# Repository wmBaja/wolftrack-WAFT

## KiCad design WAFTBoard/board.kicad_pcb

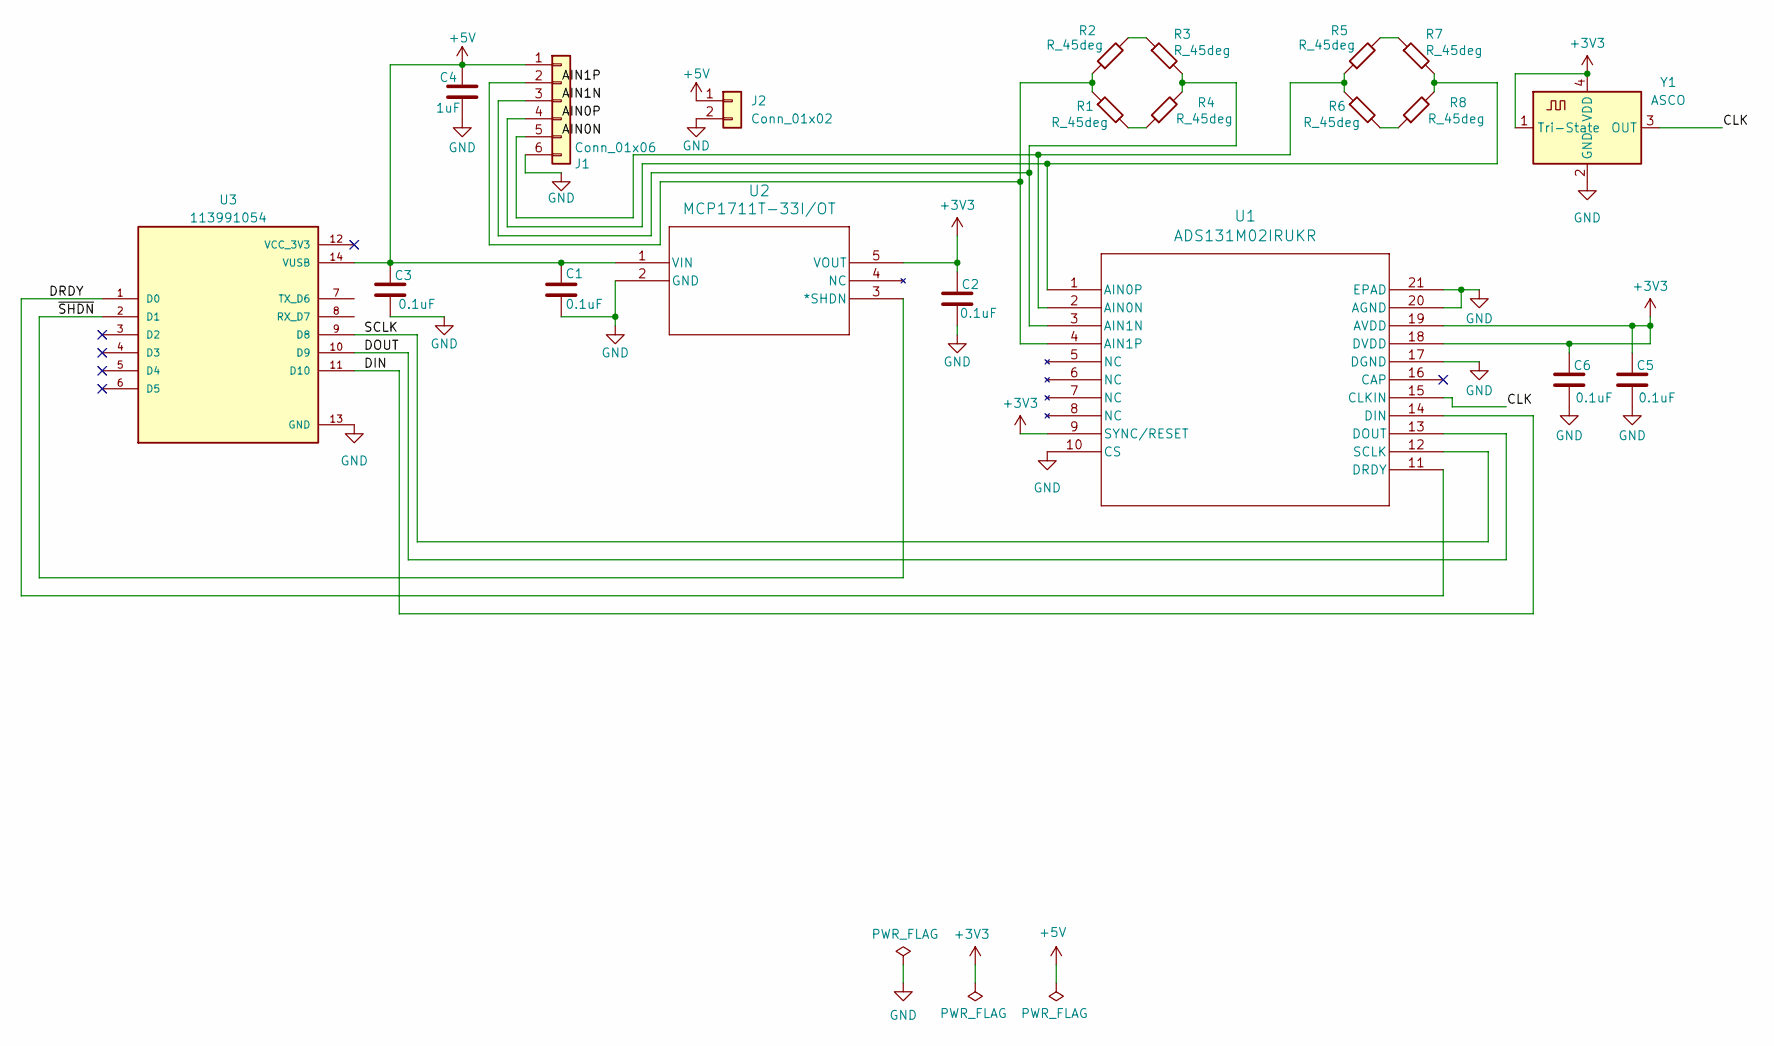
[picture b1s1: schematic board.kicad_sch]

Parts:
C1, C2, C3, C5, C6: 0.1uF; C_0805_2012Metric
C4: 1uF; C_0805_2012Metric
J1: Conn_01x06; PinHeader_1x06_P2.54mm_Vertical
J2: Conn_01x02; PinSocket_1x02_P2.54mm_Vertical
R1, R2, R3, R4, R5, R6, R7, R8: R_45deg; R_0805_2012Metric
U1: ADS131M02IRUKR; WQFN20_ADS131_TEX
U2: MCP1711T-33I/OT; SOT-23-5_OT_MCH
U3: 113991054; XIAO-ESP32-S3-SMD; PARTREV 23/05/2022
Y1: ASCO; Oscillator_SMD_Abracon_ASCO-4Pin_1.6x1.2mm

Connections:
+3V3: C2.1, C5.1, C6.1, U1.9 (SYNC/RESET), U1.18 (DVDD), U1.19 (AVDD), U2.5 (VOUT), Y1.1 (Tri-State), Y1.4 (VDD)
+5V: C1.1, C3.1, C4.1, J1.1, J2.1, U2.1 (VIN), U3.14 (VUSB)
/CLK: U1.15 (CLKIN), Y1.3 (OUT)
/DIN: U1.14 (DIN), U3.11 (D10)
/DOUT: U1.13 (DOUT), U3.10 (D9)
/DRDY: U1.11 (DRDY), U3.1 (D0)
/SCLK: U1.12 (SCLK), U3.9 (D8)
/~SHDN: U2.3 (*SHDN), U3.2 (D1)
GND: C1.2, C2.2, C3.2, C4.2, C5.2, C6.2, J1.6, J2.2, U1.10 (CS), U1.17 (DGND), U1.20 (AGND), U1.21 (EPAD), U2.2 (GND), U3.13 (GND), Y1.2 (GND)
unnamed: J1.2, R1.1, R2.1, U1.4 (AIN1P)
unnamed: J1.3, R3.2, R4.2, U1.3 (AIN1N)
unnamed: J1.4, R7.2, R8.2, U1.1 (AIN0P)
unnamed: J1.5, R5.1, R6.1, U1.2 (AIN0N)
unnamed: R1.2, R4.1
unnamed: R2.2, R3.1
unnamed: R5.2, R7.1
unnamed: R6.2, R8.1

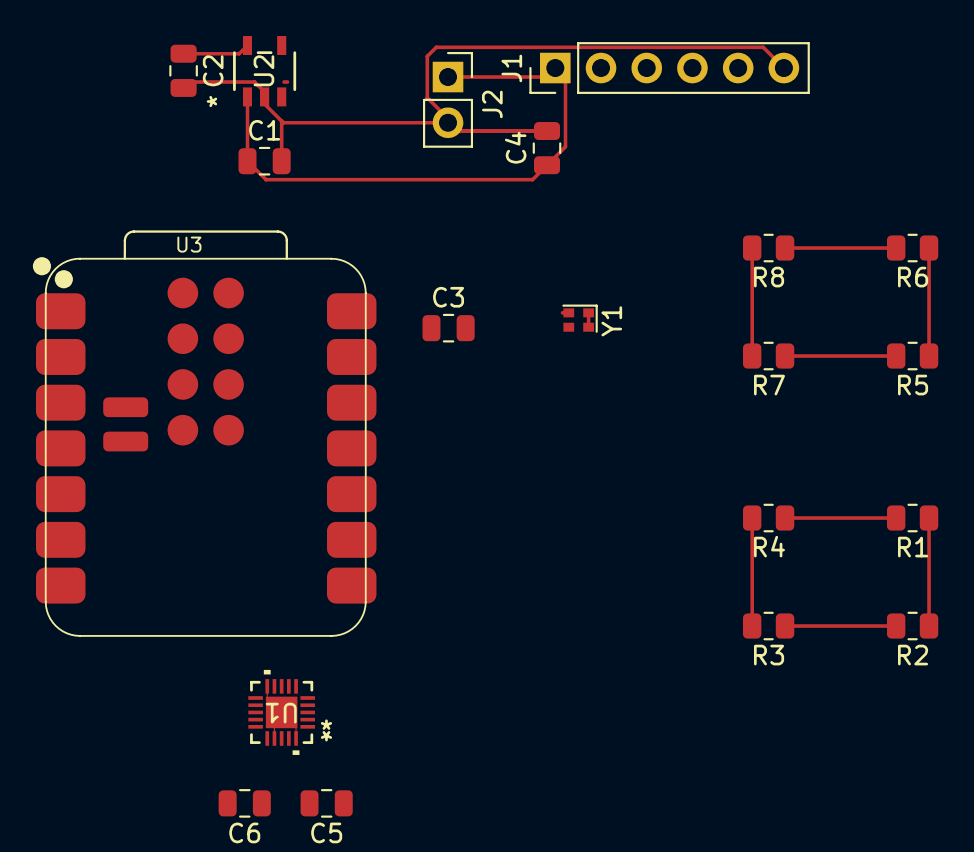
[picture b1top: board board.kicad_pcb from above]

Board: 2 copper layers, 20 parts (0 on the bottom side), 17 nets.

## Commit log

2026-01-23 First commit. Added Ardunio code and created file structure.
    Added both sender and reciever ESP32 arduino code. For use with the DOIT Devkit ESP32s.
2026-01-23 Converted projects to platformio.
    Converted to platformio, but I did not test uploading the code to the boards. The platformio code is not to fully be trusted yet!
2026-02-18 Added CAN to the reciever code so that it can work with the CAN Pal we ordered.
2026-02-20 Added efficiency to sender code.
2026-03-01 Created and tested PIO receiver code
2026-03-01 Update sender INO code for stability, MAC addr
2026-03-01 Removed dupe recv code
2026-03-01 Moved working sender code to PIO project
    Note that in the ESPNOW library used with PIO, the onSend function signature has changed.
    In Arduino, the first argument was wifi_tx_info_t *mac, but the new implementation uses uint8_t as the type. Affects line 40.
2026-03-26 First commit of new PCB design
2026-03-26 Batching for WAFT
